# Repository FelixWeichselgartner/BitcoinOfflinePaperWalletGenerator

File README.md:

# Bitcoin Offline Paper-Wallet Generator

You ever felt unsafe creating a Bitcoin wallet on your desktop computer or on your smartphone? As such devices are often connected to the internet there might be a chance you have already been hacked and somebody could be stealing your private key(s). The solution is to create your private keys on a device that cannot be hacked because it is not connected to any other devices (e.g. no internet, ...). 

This project aims for a microcontroller-based private key generation. The private key will be generated using rng. Your bitcoin address will then be calculated from your private key. Both will then be displayed on a display, for you to transfer on a piece of paper, which you will keep save. You can now use the address to transfer your bitcoins. Once you need your bitcoins, you simply import your private key in a wallet program and for safety reasons create a new paper wallet with this device. You can then use the bitcoins you need and transfer the rest to your new save bitcoin address.

## Work in progress

Only use this project at your own risk. I am not responsible for your usage of this code. Furthermore, do not send bitcoins to any addresses in this repo.

## Breadboard testbench

## PCB

Click [here](documentation/flash_pcb.md) to see how to flash a pcb.

The wires are for my revision 1 board and are already fixed in the schematic.

## RNG tests

Click [here](tests/rng_validation/TEST.md) to see the RNG tests.

## Dependencies

You can download all neccessary firmware libraries by executing `sh firmware/lib/download.sh`.

Firmware:
* https://github.com/micro-bitcoin/uBitcoin (MIT)
* https://github.com/marvinroger/ESP8266TrueRandom.git (LGPL-3.0 if ESP8266 is used)
* https://github.com/adafruit/Adafruit_BusIO (MIT, for SSD1306 display)
* https://github.com/adafruit/Adafruit-GFX-Library (BSD, for SSD1306 display)
* https://github.com/adafruit/Adafruit_SSD1306 (BSD, for SSD1306 display)

Only for address validation:
* https://github.com/PaulGregor/Bitcoin-Keys-Generator (GPL-3.0)

## License

This project is licensed under `gnu-gpl-v3.0`. See `License.txt` for more information.

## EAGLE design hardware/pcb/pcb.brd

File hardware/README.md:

# Hardware

## Testbench

## PCB

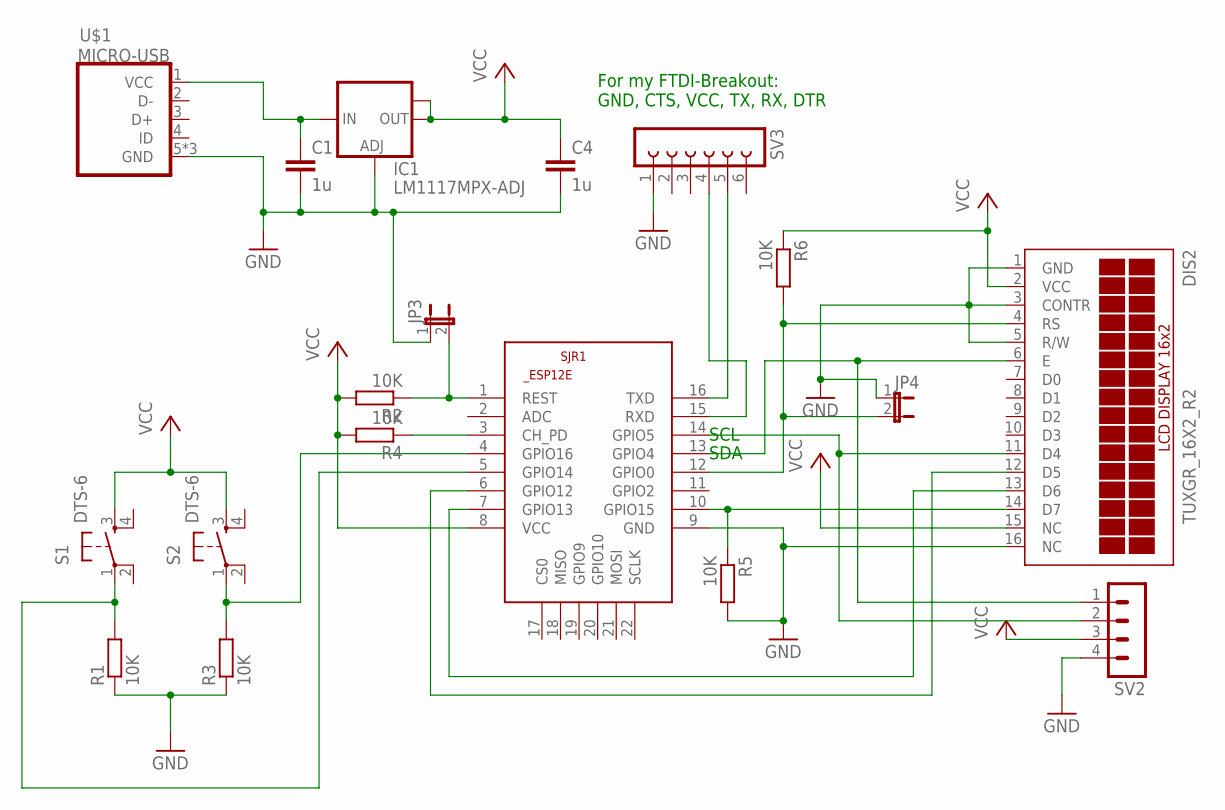
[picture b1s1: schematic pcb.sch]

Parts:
C1, C4: 1u; C0805
DIS2: TUXGR_16X2_R2
IC1: LM1117MPX-ADJ; SOT223
JP3, JP4: JP1E; JP1
R1, R2, R3, R4, R5, R6: 10K; R0805
S1, S2: DTS-6
SJR1: ESP8266-12EESP12E; ESP8266-ESP12E
SV2: MA04-1
SV3: FE06-1; FE06
U$1: MICRO-USB

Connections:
GND: C1.2, C4.2, DIS2.1 (GND), DIS2.3 (CONTR), DIS2.5 (R/W), DIS2.16 (NC), IC1.1 (ADJ), JP3.1, JP4.1, R1.1, R3.1, R5.2, SJR1.9 (GND), SV2.4, SV3.1, U$1.5 (GND), U$1.GND1 (GND), U$1.GND2 (GND)
unnamed: DIS2.11 (D4), SJR1.14 (GPIO5), SV2.2
unnamed: DIS2.12 (D5), SJR1.6 (GPIO12)
unnamed: DIS2.13 (D6), SJR1.7 (GPIO13)
unnamed: DIS2.14 (D7), R5.1, SJR1.10 (GPIO15)
unnamed: DIS2.4 (RS), JP4.2, R6.2, SJR1.12 (GPIO0)
unnamed: R3.2, S2.1, SJR1.4 (GPIO16)
unnamed: R1.2, S1.1, SJR1.5 (GPIO14)
unnamed: DIS2.6 (E), SJR1.13 (GPIO4), SV2.1
unnamed: SJR1.15 (RXD), SV3.4
unnamed: SJR1.16 (TXD), SV3.5
unnamed: C1.1, IC1.3 (IN), U$1.1 (VCC)
unnamed: JP3.2, R2.1, SJR1.1 (REST)
unnamed: R4.1, SJR1.3 (CH_PD)
VCC: C4.1, DIS2.2 (VCC), DIS2.15 (NC), IC1.2 (OUT), IC1.TAB (OUT1), R2.2, R4.2, R6.1, S1.3, S2.3, SJR1.8 (VCC), SV2.3

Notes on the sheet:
SDA
SCL
For my FTDI-Breakout: GND, CTS, VCC, TX, RX, DTR

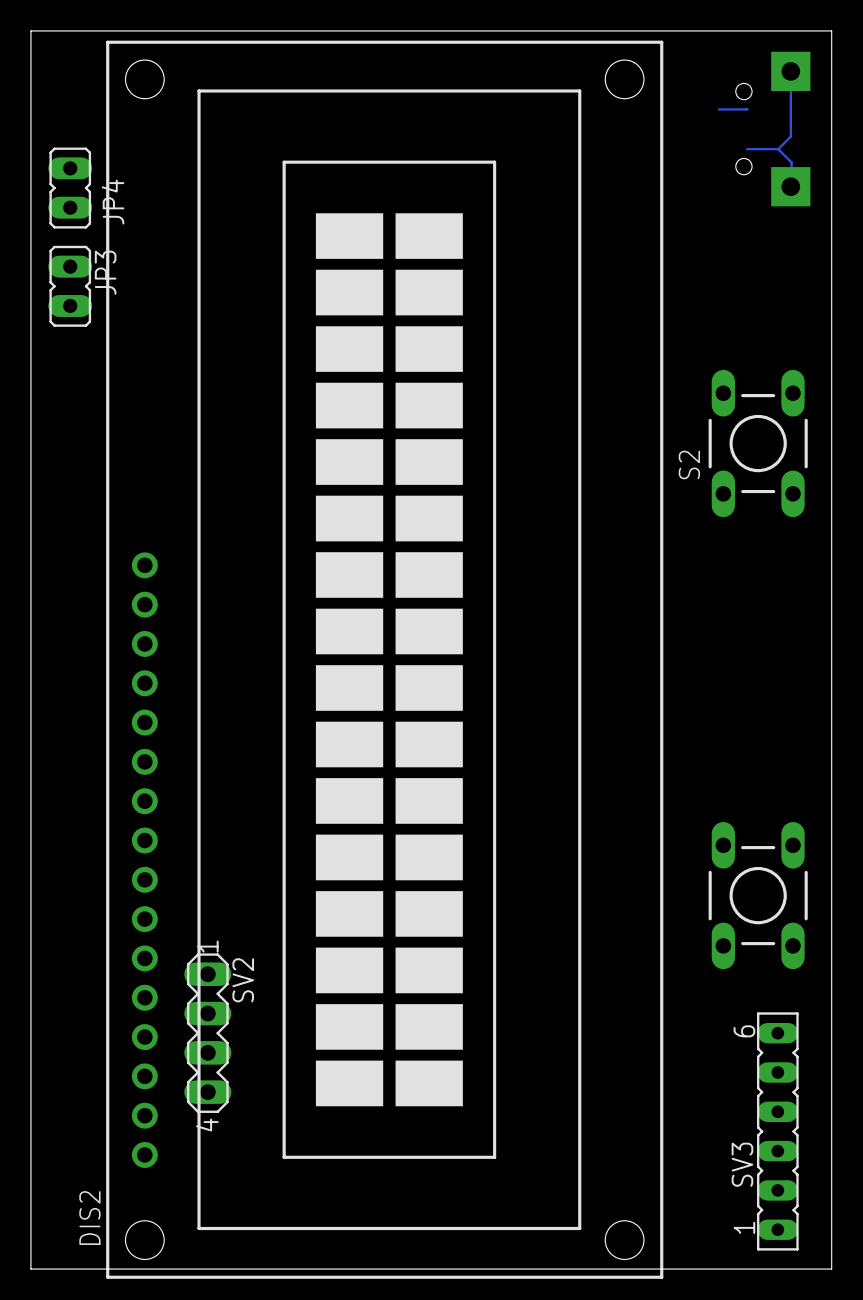
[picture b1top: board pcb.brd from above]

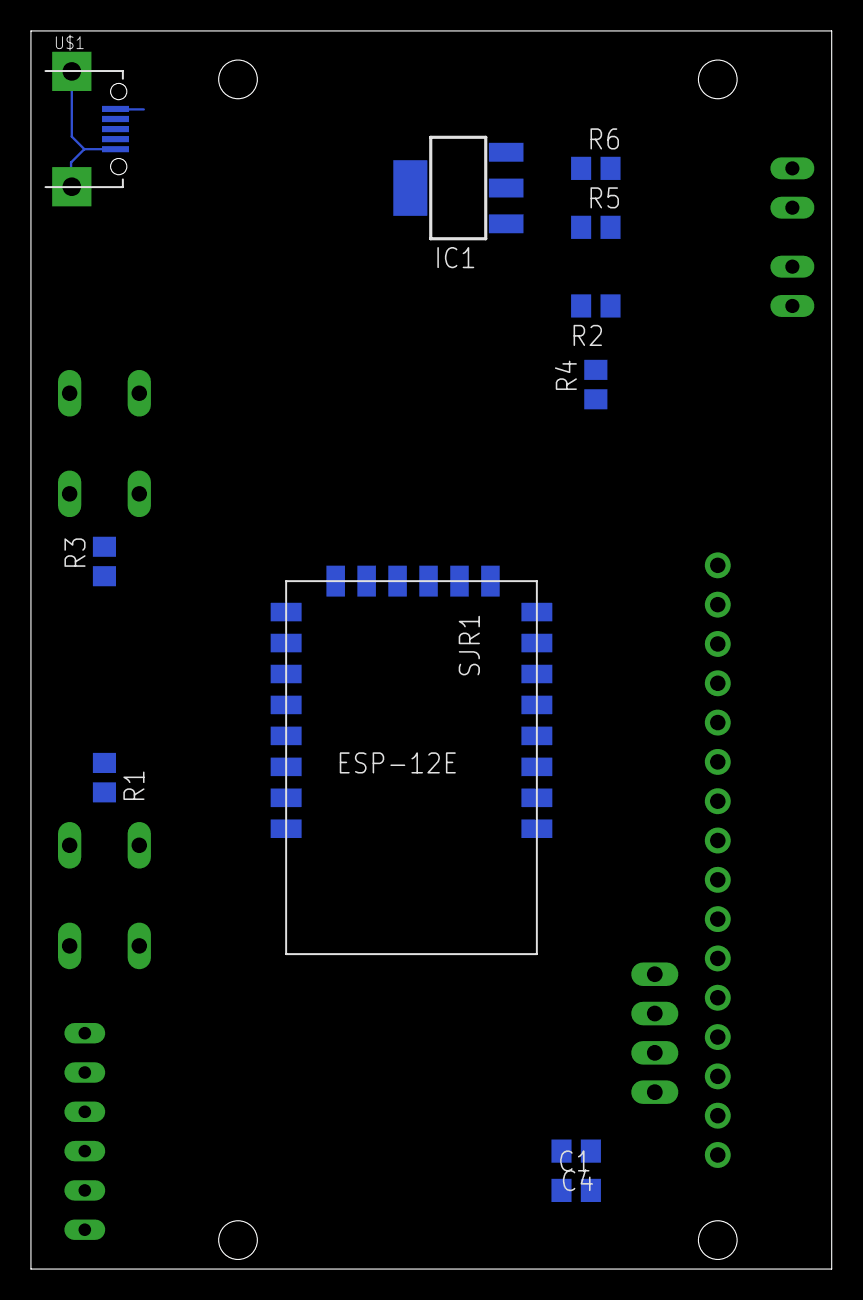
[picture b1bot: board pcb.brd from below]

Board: 2 copper layers, 51.7 x 80.0 mm, 18 parts (11 on the bottom side), 15 nets.

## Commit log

2021-03-20 initial commit; working proof of concept
2021-03-20 fixed typo
2021-03-22 implemented (true)/better-rng for esp8266
2021-03-23 added wif
2021-03-30 included testbench breadboard schematic
2021-03-30 random number distribution verification
2021-03-30 new folder structure
2021-04-01 wallet gen in own function; lcd code; all untested - compiles tho
2021-08-03 wemos d1 v2 version
2021-08-04 testbench working
2021-08-04 layout for pcb milling
2021-08-04 move wiring to bottom layer
2021-10-17 eagle pcb
2021-10-31 added support for new new display
2021-11-28 debugged pcb, which is now working
2021-11-28 spell-checked abstract
